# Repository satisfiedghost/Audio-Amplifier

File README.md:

# Audio-Amplifier
A simple audio amplifier, intended to drive larger (>25Ω) headphones.

# ToDo
I ran into some bypassing issues with the first board revision. 0.1uF caps need to be added directly to the power supplies
of U1 and U2. Additinally, U1 should have an in-loop compensation circuit added to ease driving the capacitive load.
Some footprints are too large, and could be spaced more closely.

# Notes
I chose Polypropylene as the material for my input capacitor, as they tend to have a lower distortion than others, at the
expense of a larger form factor. 0.47uF lowered the -3dB point to 3Hz, which should exhibit acceptable filtering once
the minimum range of human hearing is reached.

The 1000uF electrolytic on the power supply is likely overkill, but it certainly doesn't hurt to have if the headphones 
end up drawing large current spikes during loud parts of songs.

Some research told me that the OPA213PA op-amp is perfectly acceptable unless you're a true audiophile, in which case
a more expensive solution might be warranted.

The three bypass caps on each +- power supply are absolutey necessary, the amplifier will distort horribly without them.

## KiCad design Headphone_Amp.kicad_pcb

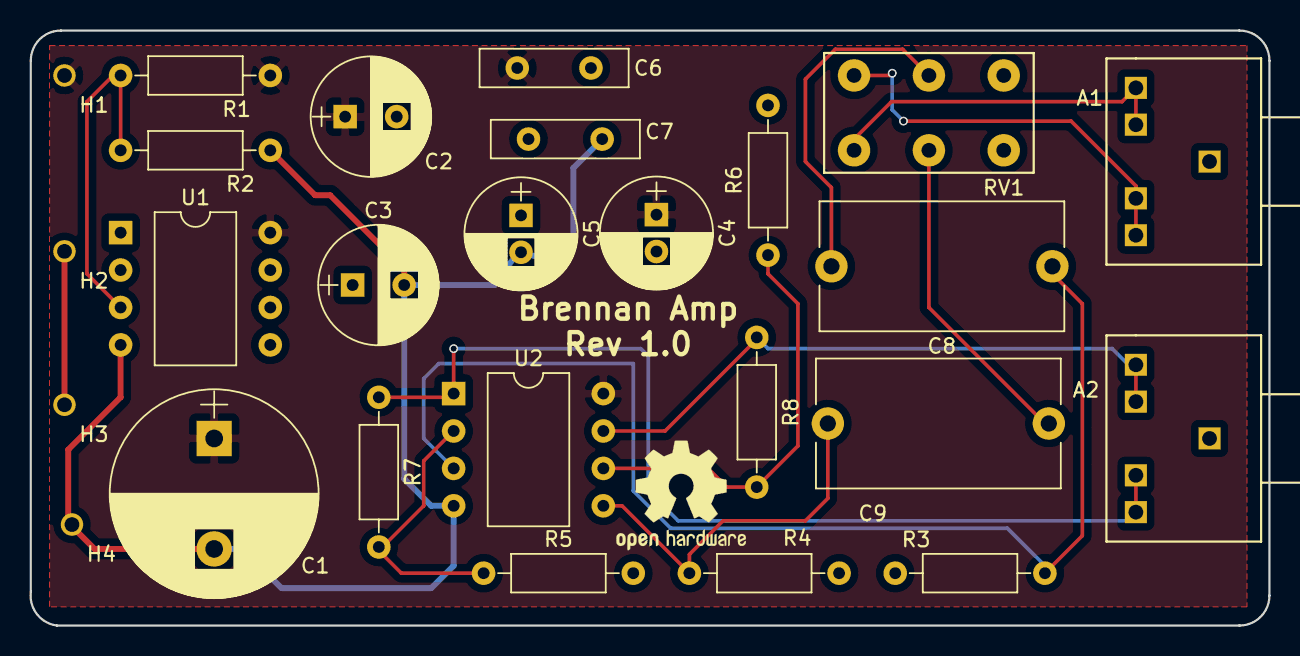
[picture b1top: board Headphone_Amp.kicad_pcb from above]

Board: 2 copper layers, 84.1 x 40.4 mm, 26 parts (0 on the bottom side), 15 nets.

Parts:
A1, A2: Audio_Jack3.5mm
C1: 1000uF; CP_Radial_D14.0mm_P7.50mm
C2, C3: 100uF; CP_Radial_D8.0mm_P3.50mm
C4, C5: 0.1uF; CP_Radial_D7.5mm_P2.50mm
C6, C7: 100pF; C_Disc_D10.0mm_W2.5mm_P5.00mm
C8, C9: 0.47uF; C_Rect_L16.5mm_W8.7mm_P15.00mm_MKT
H1, H2, H3, H4: Hole
R1, R2: 220k; R_Axial_DIN0207_L6.3mm_D2.5mm_P10.16mm_Horizontal
R3, R4: 100k; R_Axial_DIN0207_L6.3mm_D2.5mm_P10.16mm_Horizontal
R5, R6: 1k; R_Axial_DIN0207_L6.3mm_D2.5mm_P10.16mm_Horizontal
R7, R8: 4.7k; R_Axial_DIN0207_L6.3mm_D2.5mm_P10.16mm_Horizontal
RV1: 10k; DualGanged_POT
U1: LF412; DIP-8_W10.16mm
U2: OPA213PA; DIP-8_W10.16mm

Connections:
B: H2.1, H3.1
BATT_VDD: C1.1, C2.1, C4.1, C6.1, H1.1, R1.1, U1.8, U2.8
BATT_VSS: C1.2, C3.2, C5.2, C7.2, H4.1, R2.2, U1.4, U2.4
GND: A1.1, A2.1, C2.2, C3.1, C4.2, C5.1, C6.2, C7.1, R3.2, R4.2, R5.2, R6.2, RV1.3, RV1.6, U1.1, U1.2
unnamed: A1.2, A1.3, RV1.1
unnamed: A1.4, A1.5, RV1.4
unnamed: A2.2, A2.3, R7.1, U2.1
unnamed: A2.4, A2.5, R8.1, U2.7
unnamed: C8.1, R3.1, U2.3
unnamed: C8.2, RV1.2
unnamed: C9.1, R4.1, U2.5
unnamed: C9.2, RV1.5
unnamed: R1.2, R2.1, U1.3
unnamed: R5.1, R7.2, U2.2
unnamed: R6.1, R8.2, U2.6

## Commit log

2017-05-05 KiCad Files
2017-05-05 Schematic image
2017-05-05 Added image
2017-05-05 Create tmp
2017-05-11 potentiometer footprint
2017-05-11 through hole footprint
2017-05-11 Create custom libraries directory.
2017-05-11 custom libraries
2017-05-11 Updated TODO
